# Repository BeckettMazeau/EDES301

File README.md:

<h1># EDES301<h1\>
Repository for EDES301 course work

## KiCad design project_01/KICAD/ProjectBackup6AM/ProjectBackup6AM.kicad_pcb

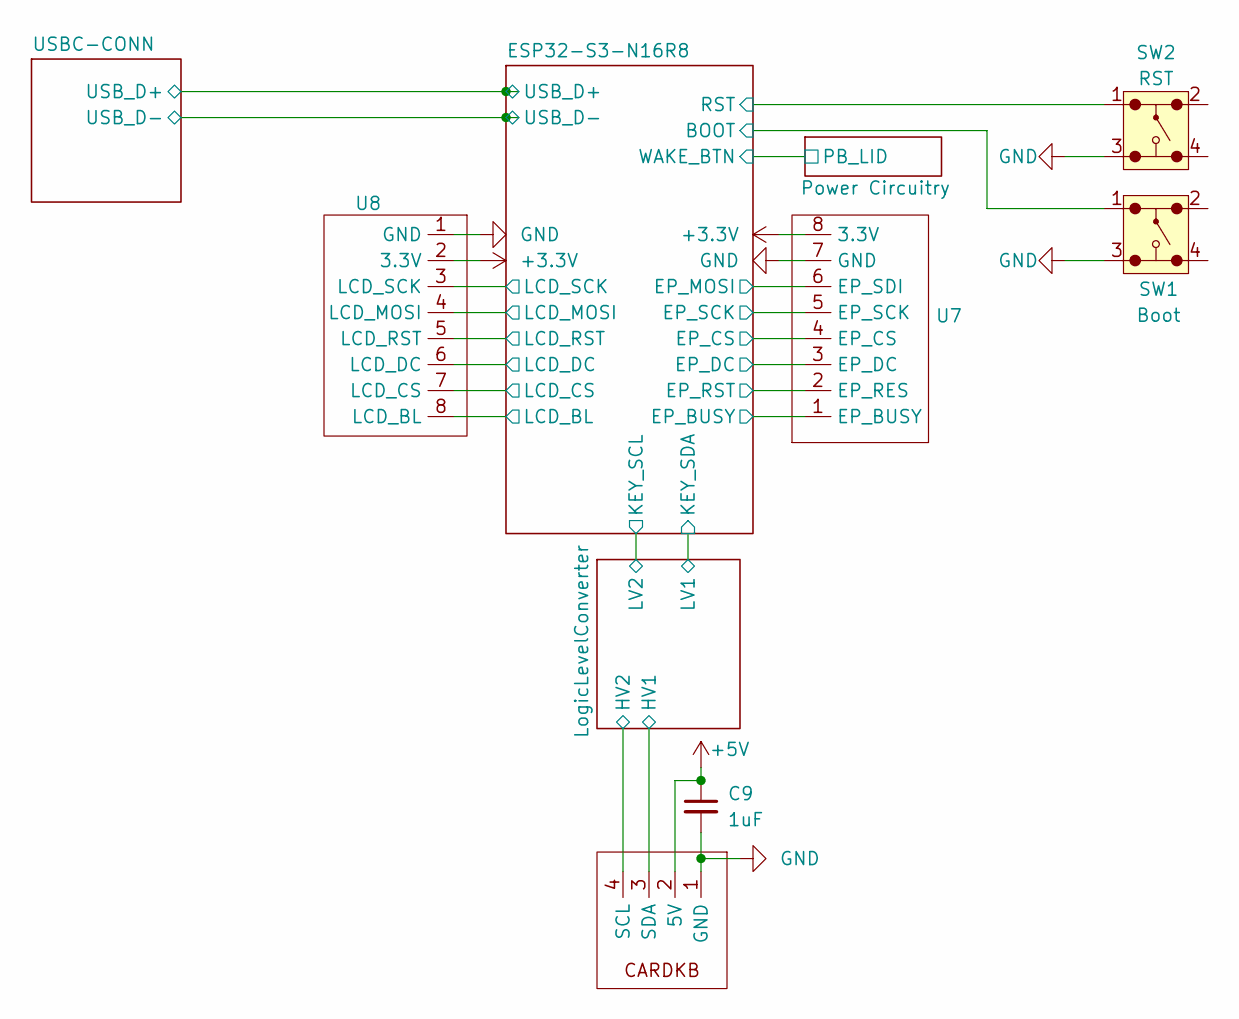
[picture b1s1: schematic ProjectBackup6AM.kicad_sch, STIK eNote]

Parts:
C9: 1uF; C_0603_1608Metric_Pad1.08x0.95mm_HandSolder
SW1: Boot; MembraneButton
SW2: RST; MembraneButton
U4: 4_Wire_Connector
U7, U8: THROUGH8

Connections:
+3.3V: U7.8 (3.3V), U8.2 (3.3V); also elsewhere on the board
+5V: C9.1, U4.2 (5V); also elsewhere on the board
/ESP32-S3-N16R8/BOOT: SW1.1; also elsewhere on the board
/ESP32-S3-N16R8/EP_BUSY: U7.1 (EP_BUSY); also elsewhere on the board
/ESP32-S3-N16R8/EP_CS: U7.4 (EP_CS); also elsewhere on the board
/ESP32-S3-N16R8/EP_DC: U7.3 (EP_DC); also elsewhere on the board
/ESP32-S3-N16R8/EP_MOSI: U7.6 (EP_SDI); also elsewhere on the board
/ESP32-S3-N16R8/EP_RST: U7.2 (EP_RES); also elsewhere on the board
/ESP32-S3-N16R8/EP_SCK: U7.5 (EP_SCK); also elsewhere on the board
/ESP32-S3-N16R8/LCD_BL: U8.8 (LCD_BL); also elsewhere on the board
/ESP32-S3-N16R8/LCD_CS: U8.7 (LCD_CS); also elsewhere on the board
/ESP32-S3-N16R8/LCD_DC: U8.6 (LCD_DC); also elsewhere on the board
/ESP32-S3-N16R8/LCD_MOSI: U8.4 (LCD_MOSI); also elsewhere on the board
/ESP32-S3-N16R8/LCD_RST: U8.5 (LCD_RST); also elsewhere on the board
/ESP32-S3-N16R8/LCD_SCK: U8.3 (LCD_SCK); also elsewhere on the board
/LogicLevelConverter/HV1: U4.3 (SDA); also elsewhere on the board
/LogicLevelConverter/HV2: U4.4 (SCL); also elsewhere on the board

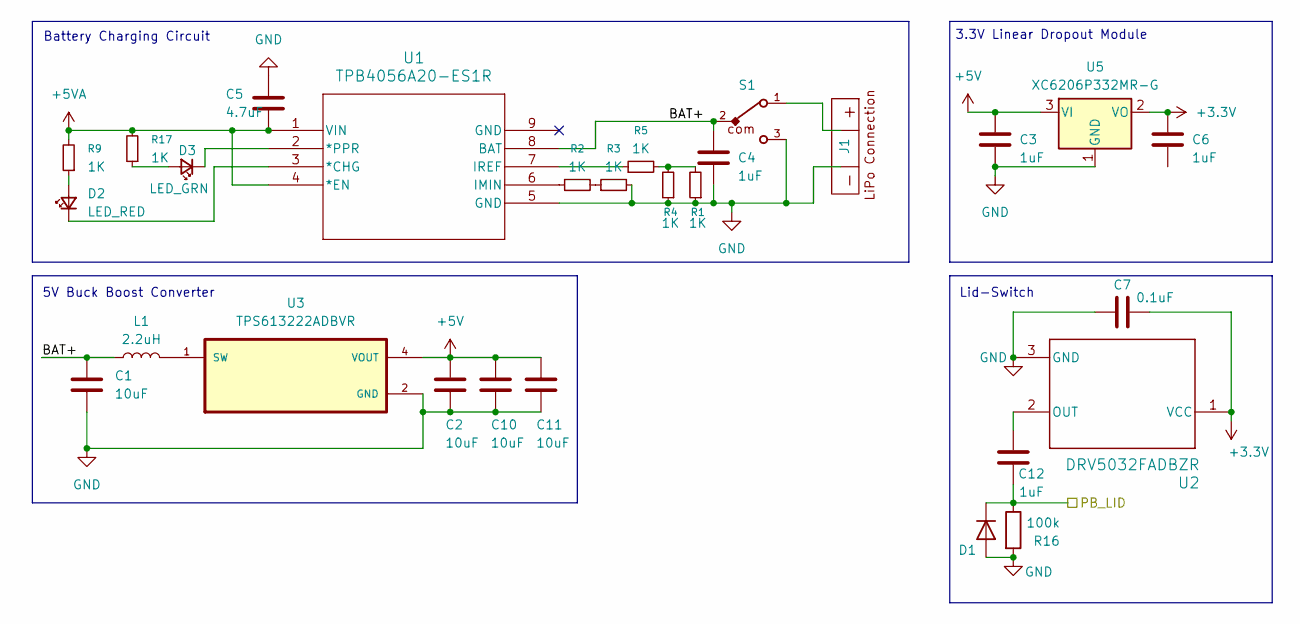
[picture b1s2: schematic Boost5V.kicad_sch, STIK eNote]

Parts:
C1, C2, C10, C11: 10uF; C_0603_1608Metric_Pad1.08x0.95mm_HandSolder
C3, C4, C6, C12: 1uF; C_0603_1608Metric_Pad1.08x0.95mm_HandSolder
C5: 4.7uF; C_0603_1608Metric_Pad1.08x0.95mm_HandSolder
C7: 0.1uF; C_0603_1608Metric_Pad1.08x0.95mm_HandSolder
D1: BAT41ZFILM; D_SOD-123
D2: LED_RED; D_0603_1608Metric_Pad1.05x0.95mm_HandSolder
D3: LED_GRN; D_0603_1608Metric_Pad1.05x0.95mm_HandSolder
J1: LipoConnection
L1: 2.2uH; IND_VLS252012ET-2R2M
R1, R2, R3, R4, R5, R9, R17: 1K; R_0603_1608Metric_Pad0.98x0.95mm_HandSolder
R16: 100k; R_0603_1608Metric_Pad0.98x0.95mm_HandSolder
S1: 450404015514
U1: TPB4056A20-ES1R
U2: DRV5032FADBZR; SOT-23-3
U3: TPS613222ADBVR; SOT95P280X145-5N
U5: XC6206P332MR-G; TSOT-23

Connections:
+3.3V: C6.1, C7.1, U2.1 (VCC), U5.2 (VO); also elsewhere on the board
+5V: C2.1, C3.1, C10.1, C11.1, U3.4 (VOUT), U5.3 (VI); also elsewhere on the board
+5VA: C5.2, R9.2, R17.2, U1.1 (VIN), U1.4 (*EN); also elsewhere on the board
/ESP32-S3-N16R8/WAKE_BTN: C12.2, D1.1 (K), R16.1; also elsewhere on the board
/Power Circuitry/: C12.1, U2.2 (OUT)
/Power Circuitry/BAT+: C1.1, C4.1, L1.1, S1.2, U1.8 (BAT)
unnamed: D2.2 (A), R9.1
unnamed: D2.1 (K), U1.3 (*CHG)
unnamed: D3.2 (A), R17.1
unnamed: D3.1 (K), U1.2 (*PPR)
unnamed: J1.1 (Batt_Pos), S1.1
unnamed: R1.2, R4.2, R5.2
unnamed: R2.2, R3.1
unnamed: R2.1, U1.6 (IMIN)
unnamed: R5.1, U1.7 (IREF)
unnamed: L1.2, U3.1 (SW)

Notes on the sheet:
5V Buck Boost Converter
Battery Charging Circuit
3.3V Linear Dropout Module
Lid-Switch

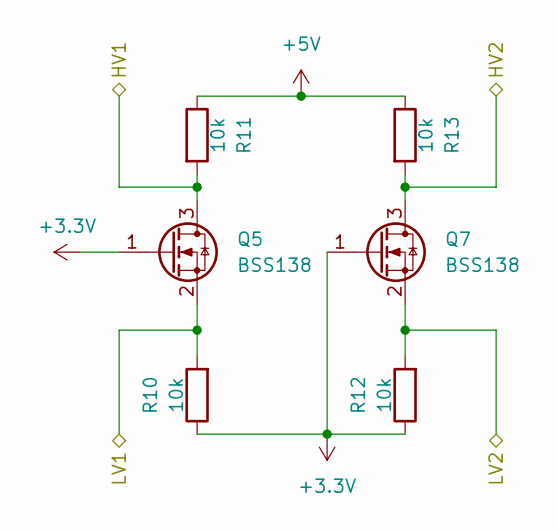
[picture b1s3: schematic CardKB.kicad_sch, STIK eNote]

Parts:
Q5, Q7: BSS138; SOT95P240X111-3N
R10, R11, R12, R13: 10k; R_0603_1608Metric_Pad0.98x0.95mm_HandSolder

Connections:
+3.3V: Q5.1 (G), Q7.1 (G), R10.1, R12.1; also elsewhere on the board
+5V: R11.1, R13.1; also elsewhere on the board
/ESP32-S3-N16R8/KEY_SCL: Q7.2 (S), R12.2; also elsewhere on the board
/ESP32-S3-N16R8/KEY_SDA: Q5.2 (S), R10.2; also elsewhere on the board
/LogicLevelConverter/HV1: Q5.3 (D), R11.2; also elsewhere on the board
/LogicLevelConverter/HV2: Q7.3 (D), R13.2; also elsewhere on the board

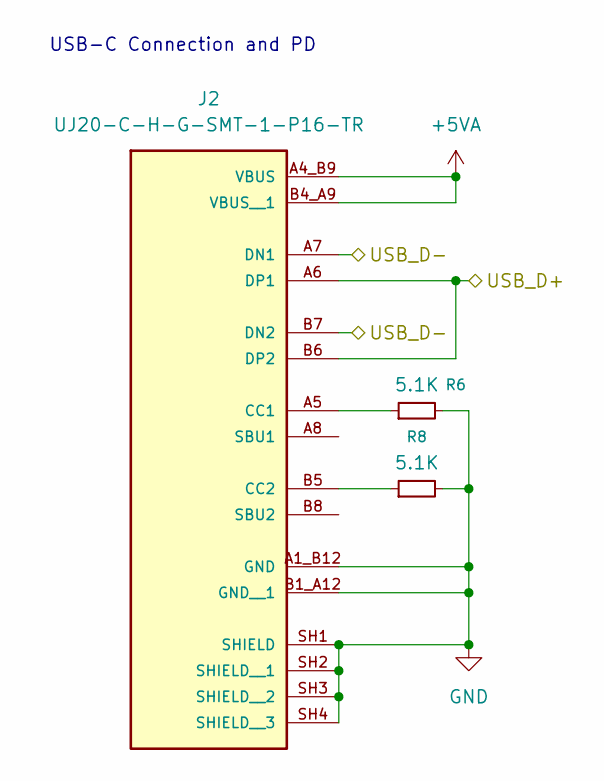
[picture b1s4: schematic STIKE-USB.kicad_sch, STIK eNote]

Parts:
J2: UJ20-C-H-G-SMT-1-P16-TR; SAMESKY_UJ20-C-H-G-SMT-1-P16-TR; PARTREV 1.0
R6, R8: 5.1K; R_0603_1608Metric_Pad0.98x0.95mm_HandSolder

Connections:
+5VA: J2.A4_B9 (VBUS), J2.B4_A9 (VBUS__1); also elsewhere on the board
/ESP32-S3-N16R8/USB_D+: J2.A6 (DP1), J2.B6 (DP2); also elsewhere on the board
/ESP32-S3-N16R8/USB_D-: J2.A7 (DN1), J2.B7 (DN2); also elsewhere on the board
unnamed: J2.A5 (CC1), R6.1
unnamed: J2.B5 (CC2), R8.1

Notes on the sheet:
USB-C Connection and PD

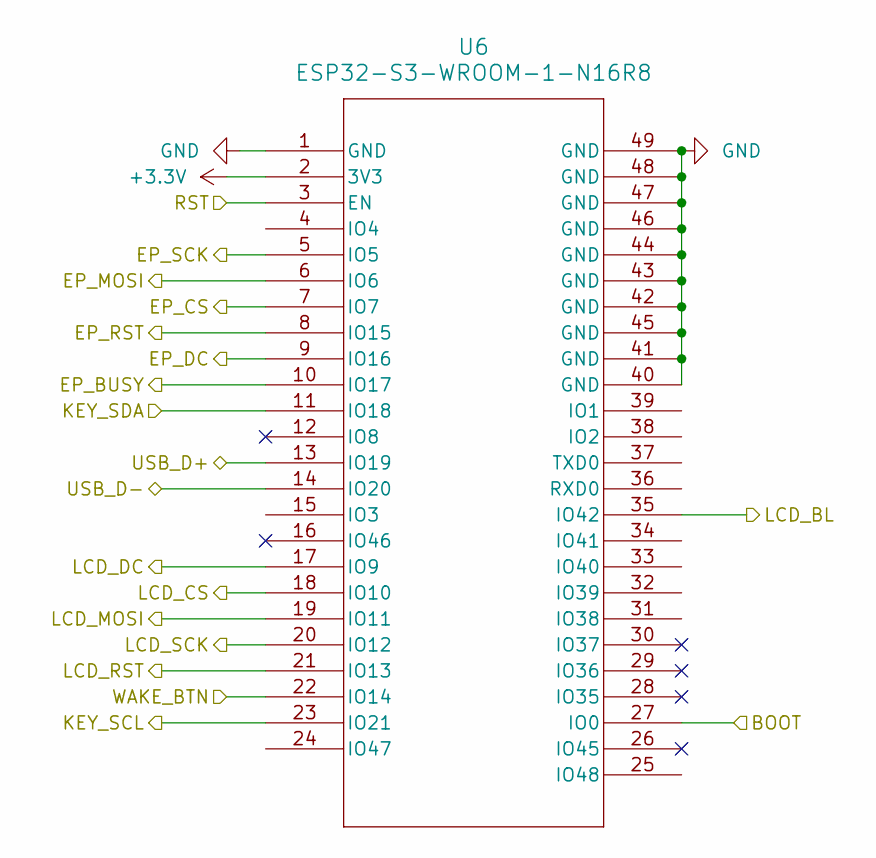
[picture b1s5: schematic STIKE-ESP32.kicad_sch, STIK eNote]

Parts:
U6: ESP32-S3-WROOM-1-N16R8; ESP32-S3-WROOM-1_EXP

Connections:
+3.3V: U6.2 (3V3); also elsewhere on the board
/ESP32-S3-N16R8/BOOT: U6.27 (IO0); also elsewhere on the board
/ESP32-S3-N16R8/EP_BUSY: U6.10 (IO17); also elsewhere on the board
/ESP32-S3-N16R8/EP_CS: U6.7 (IO7); also elsewhere on the board
/ESP32-S3-N16R8/EP_DC: U6.9 (IO16); also elsewhere on the board
/ESP32-S3-N16R8/EP_MOSI: U6.6 (IO6); also elsewhere on the board
/ESP32-S3-N16R8/EP_RST: U6.8 (IO15); also elsewhere on the board
/ESP32-S3-N16R8/EP_SCK: U6.5 (IO5); also elsewhere on the board
/ESP32-S3-N16R8/KEY_SCL: U6.23 (IO21); also elsewhere on the board
/ESP32-S3-N16R8/KEY_SDA: U6.11 (IO18); also elsewhere on the board
/ESP32-S3-N16R8/LCD_BL: U6.35 (IO42); also elsewhere on the board
/ESP32-S3-N16R8/LCD_CS: U6.18 (IO10); also elsewhere on the board
/ESP32-S3-N16R8/LCD_DC: U6.17 (IO9); also elsewhere on the board
/ESP32-S3-N16R8/LCD_MOSI: U6.19 (IO11); also elsewhere on the board
/ESP32-S3-N16R8/LCD_RST: U6.21 (IO13); also elsewhere on the board
/ESP32-S3-N16R8/LCD_SCK: U6.20 (IO12); also elsewhere on the board
/ESP32-S3-N16R8/USB_D+: U6.13 (IO19); also elsewhere on the board
/ESP32-S3-N16R8/USB_D-: U6.14 (IO20); also elsewhere on the board
/ESP32-S3-N16R8/WAKE_BTN: U6.22 (IO14); also elsewhere on the board

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
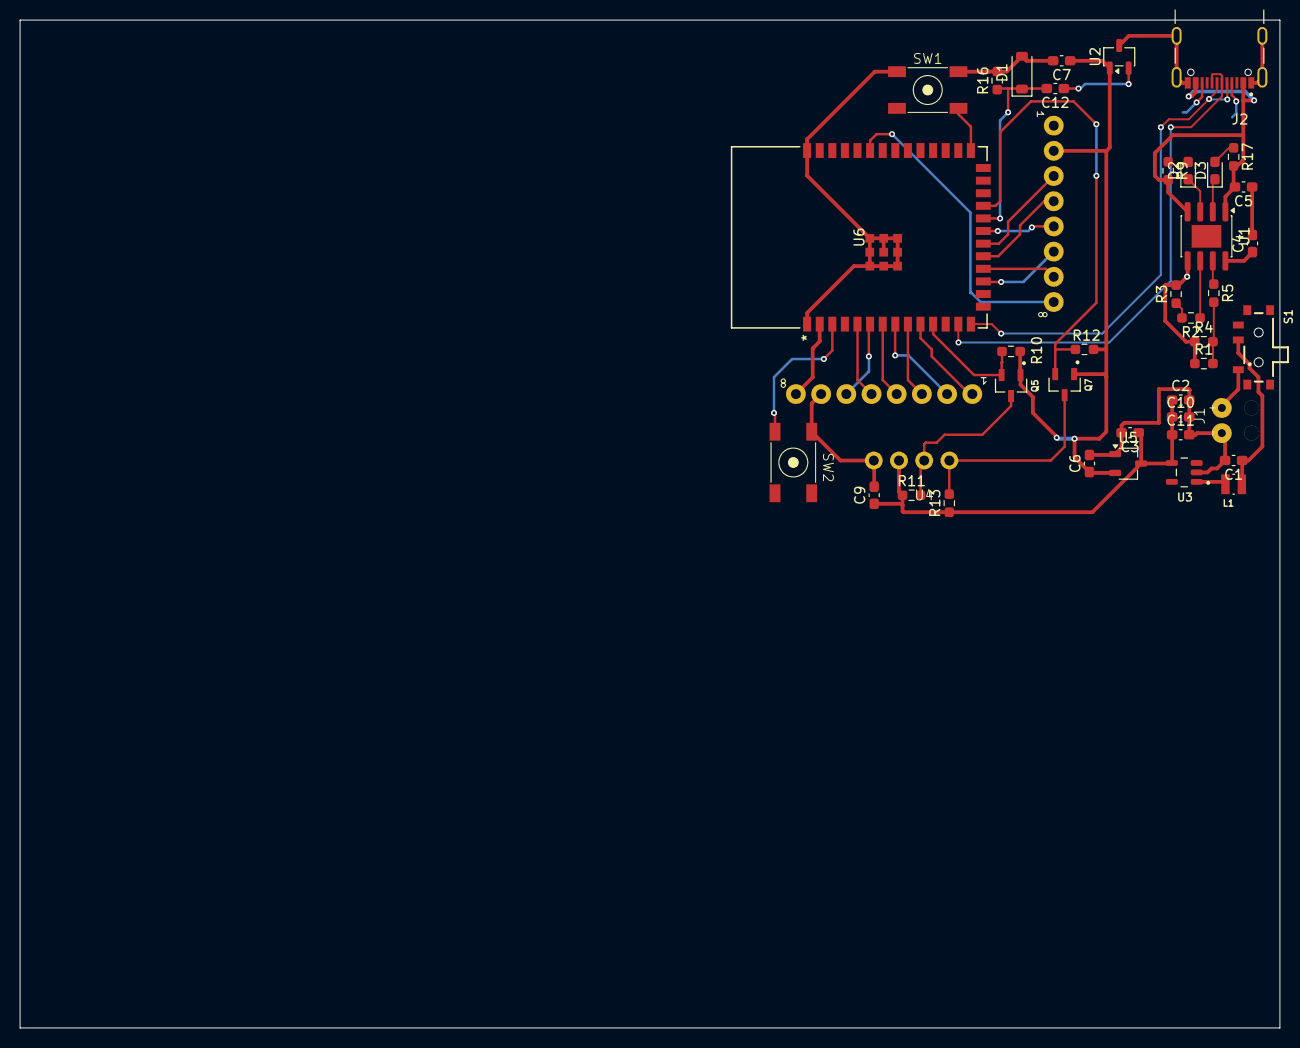
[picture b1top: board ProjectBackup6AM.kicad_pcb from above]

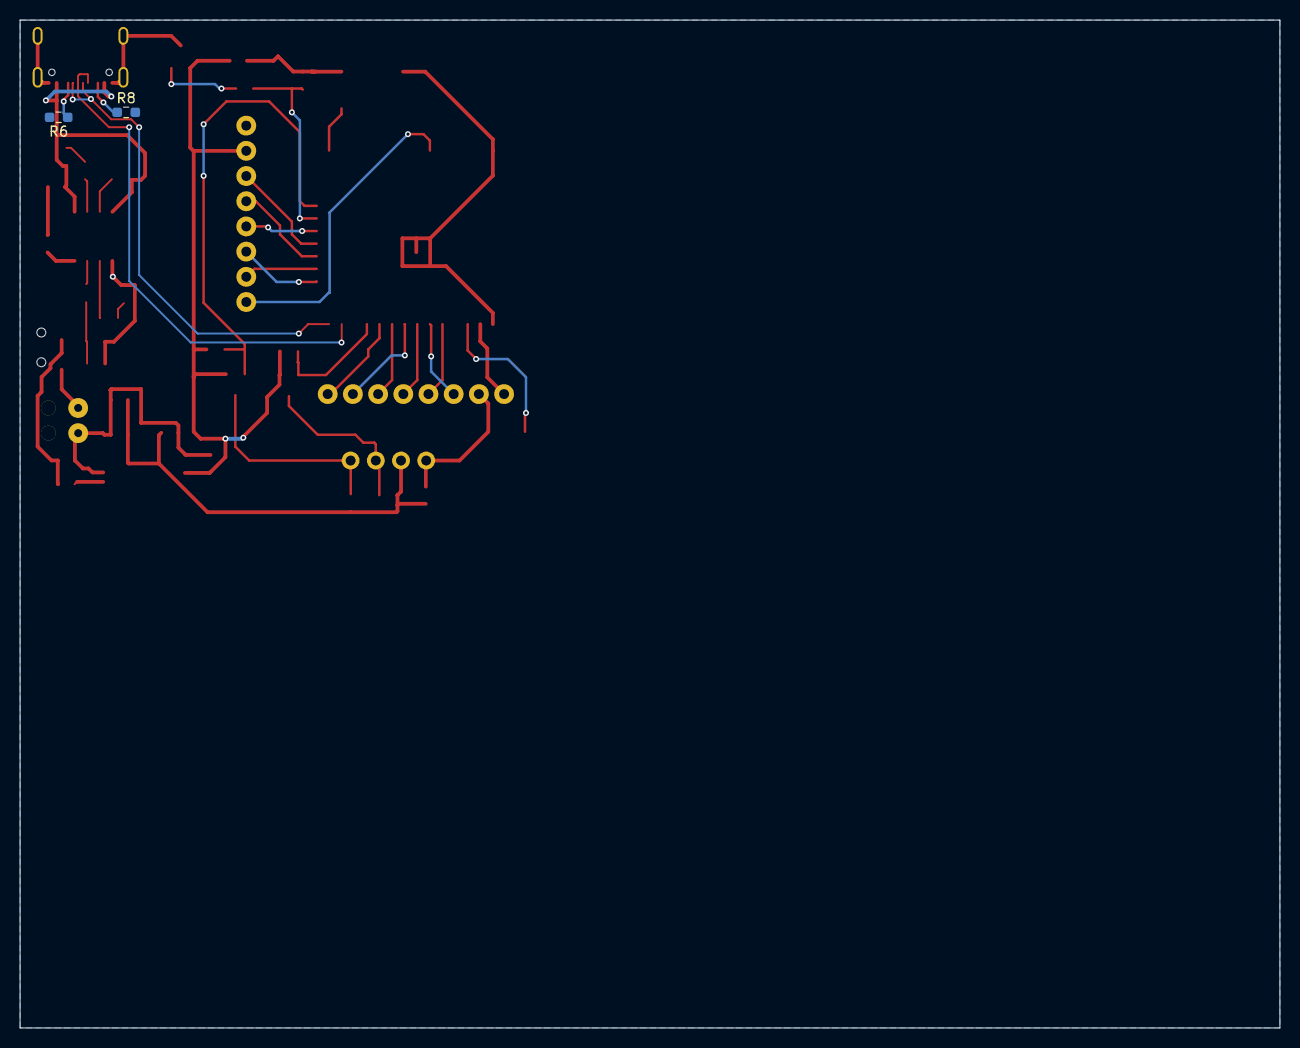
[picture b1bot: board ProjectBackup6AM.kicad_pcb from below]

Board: 2 copper layers, 127.0 x 101.6 mm, 44 parts (2 on the bottom side), 39 nets.

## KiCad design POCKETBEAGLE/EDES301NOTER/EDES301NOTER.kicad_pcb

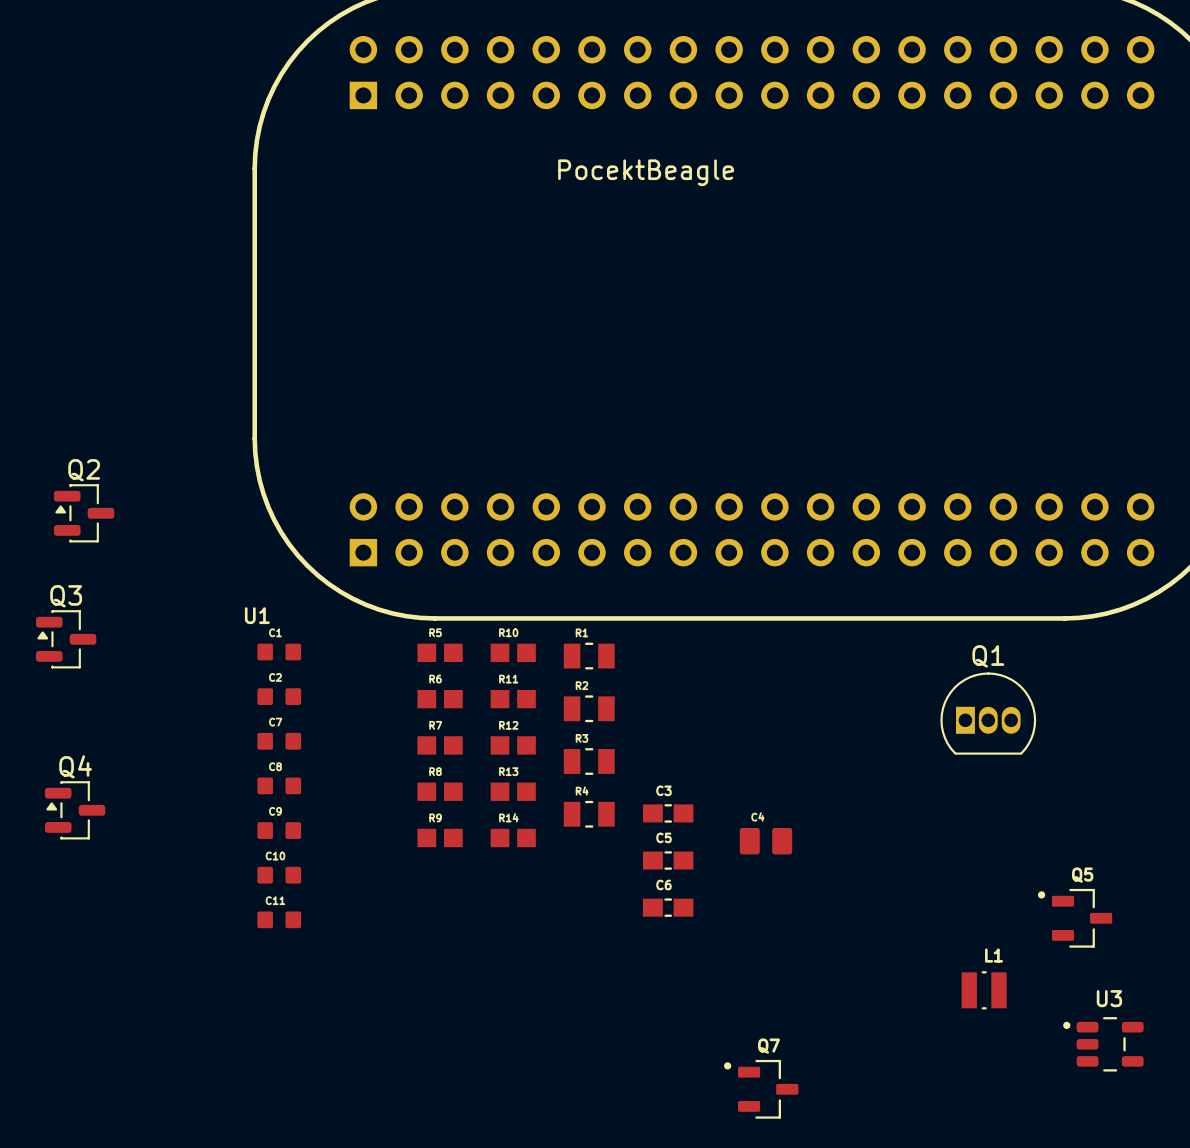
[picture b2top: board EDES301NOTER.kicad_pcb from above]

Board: 2 copper layers, 34 parts (0 on the bottom side), 14 nets, no tracks yet.

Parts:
C1, C2, C10, C11: 10uF; CAPC1608X90N
C3, C5, C6: 0.1uF; CAPC1608X90
C4: C; CAPC2012X145N
C7, C8, C9: 1uF; CAPC1608X90N
L1: 2.2uH; IND_VLS252012ET-2R2M
Q1: S8050; TO-92_Inline
Q2, Q3, Q4: BSS84; SOT-23
Q5, Q7: BSS138; SOT95P240X111-3N
R1, R2, R3, R4: 10R; RESC2012X60N
R5, R6: 1K; RESC1607X60N
R7, R8, R9: 100k; RESC1607X60N
R10, R11, R12, R13, R14: 10k; RESC1607X60N
U1: POCKETBEAGLE
U3: TPS613222ADBVR; SOT95P280X145-5N

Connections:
+3.3VA: C1.1, C3.1, C4.1, C5.1, C6.1, C7.2, C9.2, L1.1, Q2.2 (S), Q2.3 (D), Q3.2 (S), Q3.3 (D), Q4.2 (S), Q4.3 (D), Q5.1 (G), Q7.1 (G), R7.2, R8.2, R9.2, R10.1, R12.1, U1.14 (3.3V@1)
-BATT: C1.2, C2.2, C3.2, C5.2, C6.2, C7.1, C8.1, C9.1, C10.2, C11.2, Q1.1 (E), R6.2, U1.22 (GND@3), U3.2 (GND)
/+5V: C2.1, C8.2, C10.1, C11.1, R11.1, R13.1, U3.4 (VOUT)
/DATA: Q5.2 (S), Q5.3 (D), Q7.2 (S), R10.2, R11.2, R12.2, U1.6 (SPI0.CS), U1.8 (SPI0.CLK), U1.10 (SPI0.MISO), U1.12 (SPI0.MOSI), U1.45 (I2C1.SCL), U1.47 (I2C1.SDA), U1.61 (SPI1.MOSI), U1.65 (SPI1.CLK), U1.67 (SPI1.CS)
/PWM_BL_CTR: Q1.2 (B), R5.1, R6.1
unnamed: Q1.3 (C), R1.1, R2.1, R3.1, R4.1
unnamed: Q2.1 (G), R7.1, U1.44 (GPIO60)
unnamed: Q3.1 (G), R8.1, U1.20 (GPIO20)
unnamed: Q4.1 (G), R9.1, U1.56 (GPIO64)
unnamed: Q7.3 (D), R13.2
unnamed: C4.2, U1.59 (3.3V@2)
unnamed: R14.1, U1.38 (GPIO59)
unnamed: R5.2, U1.37 (PWM1A)
unnamed: L1.2, U3.1 (SW)

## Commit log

2026-02-24 init
2026-03-12 simple_calc Done
    Completed Simple Calc for HW4
2026-03-12 update simplecalc
2026-03-12 Sphinx + Fixes
2026-03-13 Notes and KICAD
    Notes doc and KICAD files moved into GITHUB REPO
2026-03-13 Updated Docs + Simple Calc Fix
2026-03-13 Simple Calc Comments and Docs
2026-03-13 Organization
2026-03-15 SoftwareWork
    Upload software flow diagram as well as did some work to understand interacting with my devices hardware.
2026-03-24 SCHEMATICV1_init
2026-03-24 goddammit
2026-03-24 UpdateSchematicV1
2026-03-24 updateschemv1
2026-03-25 SchemV2.2
2026-03-25 SchematicV2UploadPDF
2026-05-05 Revise Boost5V schematic and add STIKE symbols
    Refactor Boost5V.kicad_sch: updated title block and paper size, reorganized and renamed many symbol definitions (capacitor/inductor/diode/resistor/LED/driver), adjusted pin assignments, footprints, d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
2026-05-05 Add KiCad project files and EDES301NOTER backups
    Import new KiCad project content under project_01/KICAD: a ProjectBackup6AM project (schematics such as Boost5V.kicad_sch, HallSwitch.kicad_sch, STIKE-ESP32/STIKE-USB/TFTDisp/ePaperSupport/CardKB, PC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
2026-05-05 Update KiCad schematics to v10; clean backups
    Bump KiCad schematic version/generator to v10 and normalize symbol/property metadata in Boost5V.kicad_sch (add show_name/do_not_autoplace/hide/in_pos_files, standardize pin names/numbers/types and or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
2026-05-06 Final Class Submission
    Finalized submission of all projects, relevant files and documentation.
